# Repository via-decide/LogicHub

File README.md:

# LogicHub ⚡

**Visual architecture builder for AI-assisted app scaffolding.**

LogicHub is a browser-first node canvas for mapping an application architecture, generating a structured PRD, synthesizing file-by-file code with your own Gemini API key, and exporting the result as a ZIP. The current product is centered on the single-file UI in [`index.html`](https://github.com/via-decide/LogicHub/blob/main/index.html). [Source](https://github.com/via-decide/LogicHub/blob/main/index.html)

🌐 **Live demo:** https://via-decide.github.io/LogicHub  
📦 **Repo:** https://github.com/via-decide/LogicHub

---

## What LogicHub does

- Build an architecture visually with draggable nodes such as `UI`, `API`, `DB`, `AUTH`, `UTIL`, `CSS`, and `CFG`.
- Connect nodes to express file dependencies.
- Generate a PRD locally from the graph.
- Use your own Gemini API key to synthesize code block-by-block in the browser.
- Export synthesized output as a ZIP.
- Optionally request an APK build when deployed with the serverless API layer. [Source](https://github.com/via-decide/LogicHub/blob/main/index.html) [Source](https://github.com/via-decide/LogicHub/blob/main/api/build-apk.js)

## Current repo structure

- [`index.html`](https://github.com/via-decide/LogicHub/blob/main/index.html): canonical app UI and client logic.
- [`manifest.json`](https://github.com/via-decide/LogicHub/blob/main/manifest.json): PWA metadata.
- [`sw.js`](https://github.com/via-decide/LogicHub/blob/main/sw.js): service worker for install/offline support.
- [`api/build-apk.js`](https://github.com/via-decide/LogicHub/blob/main/api/build-apk.js): optional serverless APK build endpoint.
- [`api/publish/index.js`](https://github.com/via-decide/LogicHub/blob/main/api/publish/index.js): optional serverless publish flow for generated apps. [Source](https://github.com/via-decide/LogicHub/blob/main/index.html) [Source](https://github.com/via-decide/LogicHub/blob/main/manifest.json) [Source](https://github.com/via-decide/LogicHub/blob/main/sw.js) [Source](https://github.com/via-decide/LogicHub/blob/main/api/build-apk.js) [Source](https://github.com/via-decide/LogicHub/blob/main/api/publish/index.js)

## Local development

LogicHub does not require a bundler. For local development, serve the repository as static files so the manifest and service worker work correctly.

```bash
git clone https://github.com/via-decide/LogicHub.git
cd LogicHub
python -m http.server 8000
```

Then open `http://localhost:8000`. [Source](https://github.com/via-decide/LogicHub/blob/main/index.html) [Source](https://github.com/via-decide/LogicHub/blob/main/manifest.json)

## Usage flow

1. Add nodes from the sidebar.
2. Drag nodes to arrange the architecture.
3. Drag from a node's right port to another node's left port to create dependencies.
4. Open node config to set filename and generation instructions.
5. Click **PRD** to inspect the generated architecture brief.
6. Provide a Gemini API key and click **Synth** to generate code.
7. Click **Export** to download a ZIP.
8. Click **APK** only when running behind a deployment that exposes `/api/build-apk`. [Source](https://github.com/via-decide/LogicHub/blob/main/index.html) [Source](https://github.com/via-decide/LogicHub/blob/main/api/build-apk.js)

## Deployment notes

The GitHub Pages demo is a static deployment. Features that depend on `/api/*` routes require a server environment such as Vercel with the corresponding serverless functions configured. In particular:

- `Synth` works directly in the browser using the user's Gemini API key.
- `Export` works locally in the browser.
- `APK` requires `/api/build-apk` plus server-side Android shell tooling.
- `api/publish/index.js` requires server-side environment variables and GitHub access. [Source](https://github.com/via-decide/LogicHub/blob/main/index.html) [Source](https://github.com/via-decide/LogicHub/blob/main/api/build-apk.js) [Source](https://github.com/via-decide/LogicHub/blob/main/api/publish/index.js)

## Cleanup notes for maintainers

This repository previously contained an older map/feed prototype that no longer matched the shipped UI. The cleanup in this branch keeps the current single-file app as the source of truth and aligns documentation with the code that is actually loaded in production. [Source](https://github.com/via-decide/LogicHub/blob/main/index.html)

## License

Released under the Apache License 2.0. See [`LICENSE`](https://github.com/via-decide/LogicHub/blob/main/LICENSE).

## Public routes

LogicHub.app now has one canonical public landing page: the Sovereign Execution Boundary at `/`. The canonical editable source is `site/index.html`; run `pnpm site:build` to generate both root `index.html` and `public/index.html` with the current Git commit as `logichub-build-id`.

The existing AI App Builder is preserved at `/builder/` with a scoped builder manifest and service worker. Use `pnpm site:verify` to check source/output identity before deployment and `pnpm site:verify-live --url https://logichub.app/ --expected-commit "$(git rev-parse HEAD)"` after deployment.

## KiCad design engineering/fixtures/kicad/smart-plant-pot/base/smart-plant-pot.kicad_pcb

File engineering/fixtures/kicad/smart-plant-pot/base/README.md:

# fixtures/kicad/smart-plant-pot/base

Baseline revision of a 5V USB-powered sensor board.

**Components**: J1 (USB power), U1 (AMS1117-3.3 LDO), C1 (10uF), C2 (100nF), U2 (MCU), J2 (sensor connector), R1 (330R), D1 (LED)

**8 non-power schematic symbols**, 8 PCB footprints, 6 named nets, 15 tracks, 1 board outline.

Generated by `../generate-fixtures.mjs` with embedded lib_symbols and deterministic UUIDs.

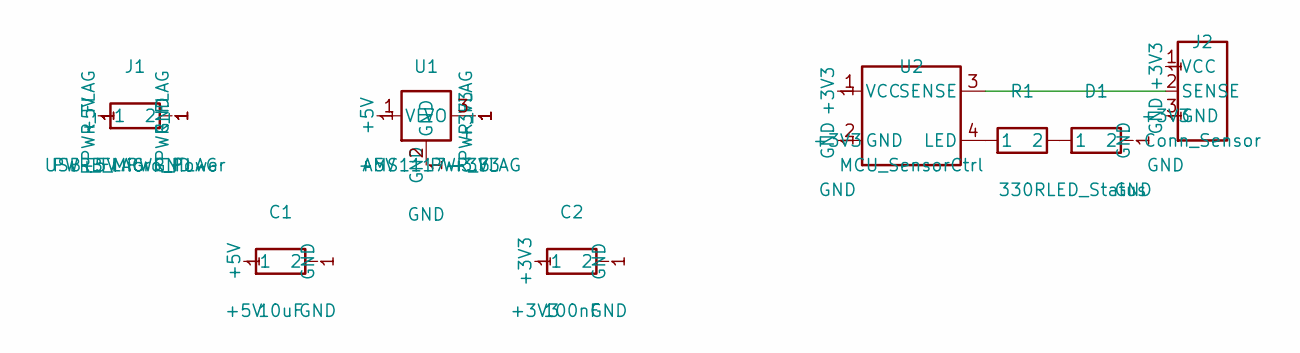
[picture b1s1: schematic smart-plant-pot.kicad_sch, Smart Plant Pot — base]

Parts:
C1: 10uF; C_0805
C2: 100nF; C_0603
D1: LED_Status; LED_0603
J1: USB_B_Micro_Power; CONN_2P
J2: Conn_Sensor; CONN_3P
R1: 330R; R_0603
U1: AMS1117-3.3; SOT-223
U2: MCU_SensorCtrl; SOIC-4

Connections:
+3V3: C2.1, J2.1 (VCC), U1.3 (VO), U2.1 (VCC)
+5V: C1.1, J1.1, U1.1 (VI)
GND: C1.2, C2.2, D1.2, J1.2, J2.3 (GND), U1.2 (GND), U2.2 (GND)
LED: R1.1, U2.4 (LED)
LED_A: D1.1, R1.2
SENSE: J2.2 (SENSE), U2.3 (SENSE)

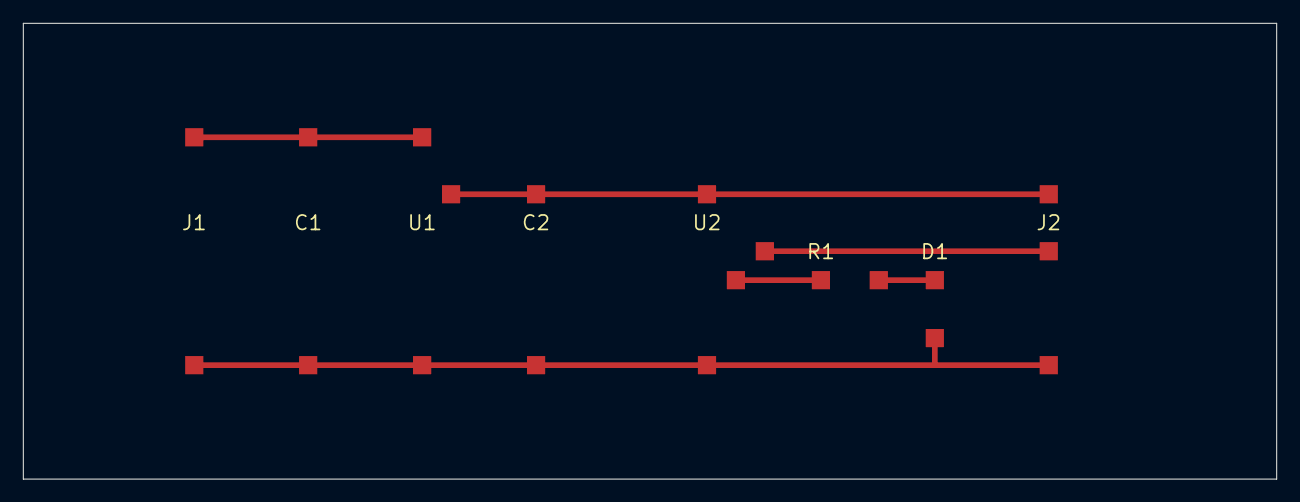
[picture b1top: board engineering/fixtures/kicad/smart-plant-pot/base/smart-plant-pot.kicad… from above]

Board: 2 copper layers, 110.0 x 40.0 mm, 8 parts (0 on the bottom side), 6 nets.

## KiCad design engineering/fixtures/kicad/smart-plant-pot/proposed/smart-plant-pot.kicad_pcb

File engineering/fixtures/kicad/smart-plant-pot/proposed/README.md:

# fixtures/kicad/smart-plant-pot/proposed

Proposed revision with controlled changes from the base:

- **J1**: USB connector → battery connector (component replacement)
- **U1**: AMS1117-3.3 LDO → TPS62A02 buck regulator (component replacement)
- **D2**: Schottky diode added (new component)
- **R1, D1**: Status LED circuit removed (component removal)
- **C3**: Additional 100nF cap added (BOM quantity change)
- **J2**: Sensor connector moved to new position (placement change)

These changes exercise the diff engine's ability to detect replacements, additions, removals, quantity changes, and geometry-only moves.

Generated by `../generate-fixtures.mjs` with embedded lib_symbols and deterministic UUIDs.

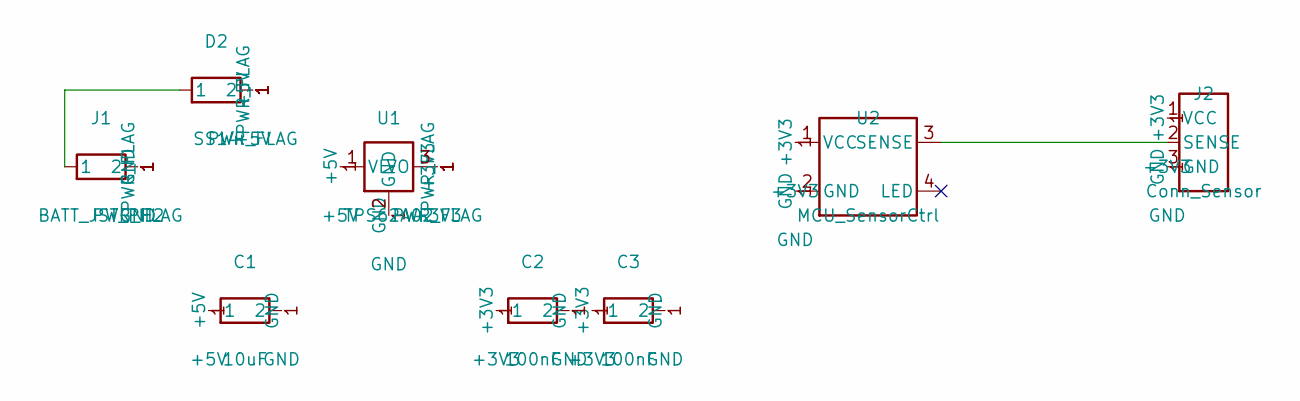
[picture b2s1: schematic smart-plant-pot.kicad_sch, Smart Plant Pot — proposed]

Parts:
C1: 10uF; C_0805
C2, C3: 100nF; C_0603
D2: SS14; D_SMA
J1: BATT_JST_PH2; CONN_2P
J2: Conn_Sensor; CONN_3P_Vertical
U1: TPS62A02; SOT-23-5
U2: MCU_SensorCtrl; SOIC-4

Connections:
+3V3: C2.1, C3.1, J2.1 (VCC), U1.3 (VO), U2.1 (VCC)
+5V: C1.1, D2.2, U1.1 (VI)
GND: C1.2, C2.2, C3.2, J1.2, J2.3 (GND), U1.2 (GND), U2.2 (GND)
SENSE: J2.2 (SENSE), U2.3 (SENSE)
VIN: D2.1, J1.1

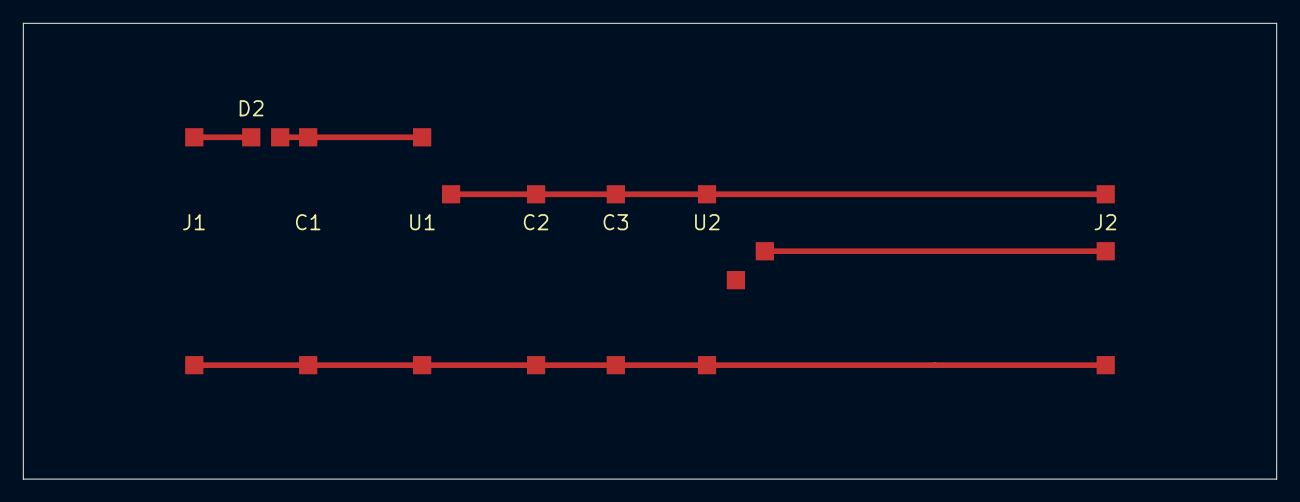
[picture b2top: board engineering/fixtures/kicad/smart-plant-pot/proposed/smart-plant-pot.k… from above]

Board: 2 copper layers, 110.0 x 40.0 mm, 8 parts (0 on the bottom side), 5 nets.

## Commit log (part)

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2026-03-30 feat: add LogicHub architecture and browser prototype
2026-03-30 feat: add PWA manifest, service worker, and install metadata
2026-03-30 fix: add install prompt logic and update PWA caching strategy
2026-03-31 fix: resolve 404 service worker and clean up PWA install logic
2026-03-31 fix: keep install button visible in UI
2026-03-31 fix: update PWA paths to relative for GitHub Pages and remove duplicate listeners
2026-03-31 Update LICENSE
2026-03-31 Install and configure Vercel Web Analytics
    ## Vercel Web Analytics Installation
    Successfully installed and configured Vercel Web Analytics for this vanilla JavaScript project.
    ### Project Analysis
    - **Framework**: Vanilla JavaScript (no build system or package manager)
    - **Project Type**: Static HTML/CSS/JS application (LogicHub v2)
    - **Main Entry Point**: index.html
2026-03-31 Install Vercel Web Analytics for project
    ## Vercel Web Analytics Configuration Complete
    ### Summary
    Successfully configured Vercel Web Analytics and Speed Insights for the LogicHub project following the latest official documentation from Vercel.
    ### Changes Made
    **Modified:**
    - `index.html` - Updated analytics configuration in the `<head>` section
2026-03-31 fix: force inject Daxini Forge UI and wire synthesis button
2026-03-31 feat: inject Daxini Forge modal, FAB, and Vercel API integration
2026-03-31 ui: relocate forge button to header and clarify BYOK input
2026-03-31 feat: implement 3x3 Engine Sandbox for dynamic internal PRD assembly
2026-03-31 fix: APK asset injection and empty-build guard
2026-04-01 fix: resolve unknown ? placeholder in node counter UI
2026-04-01 feat: tour steps populated with real onboarding content
2026-04-01 fix: header logo and badge text separation
2026-04-01 fix: install button hidden until valid APK is generated
2026-04-01 fix(apk): asset injection order, size guard, step progress, zip fallback
2026-04-01 fix: live debug sweep — counter, tour, APK gate, status dot, pro CTA, tooltip
2026-04-01 feat: overhaul internal PRD engine and reset counter logic
2026-04-01 feat: encode decision UX conversion mandates into PRD directives
2026-04-01 feat: complete directive coverage and add codex repo instructions
2026-04-02 feat: initial commit of LogicHub v2
2026-04-02 fix: load people from root-level people-registry.json
2026-04-02 feat: cleanup stale prototype files and align docs with shipped app
2026-04-02 feat: simplify labels and publish into contextual store routes
2026-04-02 feat: add founder UPI checkout and plainer part labels
2026-04-02 feat: polish founder pass sales ux
2026-04-02 chore: add manual founder confirmation note
2026-04-02 feat: premium founder flow polish and onboarding layer
2026-04-02 feat: add server-verified paid access with Firebase
2026-04-02 feat: reframe logichub for google and ai seo
2026-04-02 fix: restore mobile scrolling on founder polish layout
2026-04-02 fix: restore mobile page scrolling in builder
2026-04-02 fix: tune mobile behavior for safari chrome and samsung
2026-04-02 fix: handle founder payment manually and notify by email
2026-04-02 chore: add minimal vercel config for production sync
2026-04-02 fix: repair forge reset timing window
2026-04-02 feat: add firebase public feed and app view analytics endpoints
2026-04-15 chore: expand codex agent operating instructions
2026-04-15 chore: align codex instructions with provided canonical text
2026-04-20 feat: add modular landing and workspace UX redesign
2026-04-20 feat: add blueprint save, share, import, and library flows
2026-04-20 feat: add daxini publish pipeline endpoint and client wiring
2026-04-20 feat: surface builder capabilities with landing actions and templates
2026-04-20 feat: add builder starter templates and template CTA
2026-04-20 fix: stabilize static deployment build and runtime checks
2026-04-20 fix: stabilize static deployment build and routing
2026-04-20 feat: add LogicHub Studio visual builder interface
2026-04-20 feat(studio): integrate zayvora workflow auto-generation
2026-04-20 feat(workflow): add parser/compiler/runtime execution engine
2026-04-20 feat(generator): add workflow-to-app generation pipeline
2026-04-20 feat(deployment): add deploy manager and target adapters
2026-04-20 feat(marketplace): add Daxini publish integration for built apps
2026-04-20 feat: add creator template gallery and starter graph cloning
2026-04-20 feat(runtime): add lightweight browser workflow runtime engine
2026-04-21 fix(deploy): restore vercel build output pipeline
2026-04-21 fix: restore vercel routing and codex instruction baseline
2026-04-21 fix(deploy): stabilize vercel public output generation
2026-04-21 feat(deploy): add bulk Vercel redeploy recovery script
2026-04-21 feat: redesign studio builder for mobile-first workflow
2026-04-21 feat: implement mobile-first studio builder shell
2026-04-21 feat: redesign studio canvas interactions for mobile performance
2026-04-21 feat: simplify mobile builder to canvas-first 4-action toolbar
2026-04-21 feat(runtime): add centralized reactive app state engine
2026-04-21 feat(workflow): add trigger/action model and runtime executor
2026-04-21 feat: add voice-driven AI builder planning flow
2026-04-21 feat(studio): add hybrid entry modes with ai and voice builder
2026-04-21 feat: upgrade studio builder for desktop layout
2026-04-21 chore: expand codex guardrails and static deployment policy
2026-04-21 feat: harden auth, payments, publishing, and admin moderation flows
2026-04-21 feat: stabilize marketplace runtime telemetry and discovery APIs
2026-04-21 feat: stabilize marketplace discovery and tracking runtime
2026-04-22 fix: resolve Vercel deployment failure by migrating deprecated routes to rewrites
2026-04-22 ui: optimize product-builder mobile layout and fix CTA visibility
2026-04-24 feat: transform LogicHub into viral app distribution engine
2026-04-24 fix: resolve build:vercel failure and update vercel deployment config
2026-04-24 fix: remove invalid rootDirectory from vercel.json
2026-04-24 fix: bypass vercel function limits using edge runtime and .vercelignore
2026-04-30 Initialize Zayvora control bootstrap files
2026-05-01 Add publish-image route: structures prompt, generates image, commits .zay to daxini.space
2026-05-06 Add feature-flagged Zayvora execution and verification layer
2026-05-06 Connect studio sections through shared execution engine
2026-05-06 Fix studio engine wiring to use deterministic global load
2026-05-06 Wire flow engine to live studio graph state
2026-05-06 Harden studio flow execution and engine fallback
2026-05-06 fix: enable scrolling, remove vercel dependency, sovereign stack config
    - Fix body overflow: hidden preventing page scroll
    - Set main-container to 85vh with 700px min-height
    - Add smooth scroll behavior
    - Remove vercel.json (backed up as .sovereign_bak)
    - All deployment now via local PM2 sovereign stack
2026-05-06 fix: bypass Vercel 12-function limit — ignore api/ dir, pure static deploy
2026-05-06 fix: disable build command — pure static deploy
2026-05-06 feat: replace Firebase auth with Aporaksha sovereign JWT auth
    - Remove Firebase SDK scripts (firebase-app-compat, firebase-auth-compat)
    - Replace FIREBASE_CONFIG with APORAKSHA_AUTH_URL (aporaksha.com/api)
    - Add JWT token storage (localStorage)
    - Add aporaksha_login, aporaksha_signup, aporaksha_logout methods
    - Replace Firebase getIdToken with stored JWT Bearer token
    - Auth now works without Firebase project — zero cloud dependency
2026-05-08 feat: implement 100% sovereign zayvora pipeline and fix publish route
2026-05-13 feat: Integrate 223-trace Zayvora Sovereign Engine + Geo-Locking Logic
2026-05-13 feat: Upgrade LogicHub to RAG-Enhanced 6-Stage Vibecoding Engine
2026-05-13 feat: upgrade Stage 1 PRD to world-class markdown synthesis + RAG-enhanced Stage 6
2026-05-20 Scaffold behavioral event, ingestion, and temporal storage foundations
2026-06-04 Fix Razorpay alert → WhatsApp checkout + favicon + legal docs — shoot ready
2026-06-12 feat: integrate pricing, templates, and student validation
2026-06-13 [Cockpit] Cross-dependency and CORS debugging sync
2026-06-13 [Cockpit] NPM Security: Hardened token protection and .gitignore updates
2026-06-13 fix: explicit CORS handling for OPTIONS preflight in serverless functions
2026-06-13 feat(pricing): implement database-driven regional pricing and geofencing for IN/Global tiers
2026-06-13 feat(backend): wire zayvora bundle_zay python engine
2026-06-13 feat(pricing): update pricing page to load dynamic eligibility rules
2026-06-16 feat: canvas-first onboarding restructure — progressive disclosure system v1
    - Canvas Workspace promoted to root view (fills full viewport, no scroll)
    - All marketing sections hidden from layout flow (landing hero, builder lanes,
    onboarding card, helper strip, ecosystem footer) — moved to disclosure panels
    - Start Building CTA added to canvas hint with pulse animation
    - Disclosure overlay: 6-card tray (What / How It Works / Templates /
    Publish+APK / Founder Access / Ecosystem) appears on CTA click
2026-06-16 fix: CORS preflight handling at edge and backend
    - vercel.json: Add global CORS edge headers for /api/* routes to prevent 405 Method Not Allowed on OPTIONS preflights
    - api/server.js: Configure Express cors() to explicitly accept X-Ecosystem-Uid header
2026-06-16 feat: LogicHub Artifact Generation Engine - comprehensive 14-section Zayvora blueprint, UI panel, and export packaging
2026-06-16 feat(commerce): enforce strict checkout geofencing for IN, LU, JP with UI updates
2026-06-16 feat: share link generation for viral loop
2026-06-16 feat: Integrate zayvora:engineer local Ollama model with Cockpit v0.3 Supervisor Loop
2026-06-16 feat(ui): add high-production UX onboarding carousel with interception logic
2026-06-16 refactor(ui): progressive disclosure architecture to hide complex ecosystem features until post-activation
2026-06-16 refactor(ux): rewrite logicHub activation flow for artifact ownership and force onboarding for new users
2026-06-17 fix: add missing ecosystem-nav.js and ecosystem.css files
2026-06-17 feat: add pulsing publish CTA animation and footer priority links relocation
2026-06-17 feat(logichub): compile output to YAML manifests/project logic and raw ARCHITECTURE_PRD
2026-06-17 feat(ui): update hero positioning copy to 'Describe App -> Get APK', add sticky ecosystem bar, and standardize universal footer
2026-06-17 UX/UI Audit: Add focus-visible styling, increase touch targets, and ARIA labels
2026-06-17 Fix missing analytics script causing MIME type issue
2026-06-17 Fix: Revert accidental deletion of onboarding flow and Zayvora bridge
2026-06-17 feat: install canonical mobile-first onboarding flow
    - Replace onboarding.html with 4-screen mobile-first activation funnel
    - Add onboarding gate to index.html (redirects to /onboarding if not complete)
    - Add /forge and /onboarding routes to sovereign_edge.mjs
    - Update vercel.json with /forge rewrite rules
    Screens: Build Apps You Actually Own → Every File Is Yours → Not Output. Software. → The Complete Artifact
    Flow: /onboarding → enterForge() → sets onboarding_complete=true → /forge → index.html
2026-06-18 feat: add onboarding telemetry, accessibility focus rings, and update analytics constraints
2026-06-18 fix: migrate to sovereign auth, fix firebase admin deps, sync public/api
2026-06-18 fix(publish): fallback to daxini edge when github tokens are missing
2026-06-18 chore(config): optimize vercel routing and implement edge caching
2026-06-18 fix(security): lock down CORS and add payload size limit
2026-06-19 feat: integrate Aporaksha passports and Zayvora deterministic builder, remove legacy UTR flow
2026-06-19 feat(auth,db): add conditional logging for swallowed catches in development mode
2026-06-19 perf(export): increase PM2 memory restart threshold and parallelize GitHub publish uploads
2026-06-19 fix: unblock Next.js build compilation (Google Fonts & Webpack swap)
2026-06-24 feat(security): implement server-side IP rate limiting on Zayvora synthesis endpoints
2026-06-30 fix: resolve tailwind check crash and simplify string templating for ES compatibility

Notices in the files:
README.md:
License: Apache 2.0
